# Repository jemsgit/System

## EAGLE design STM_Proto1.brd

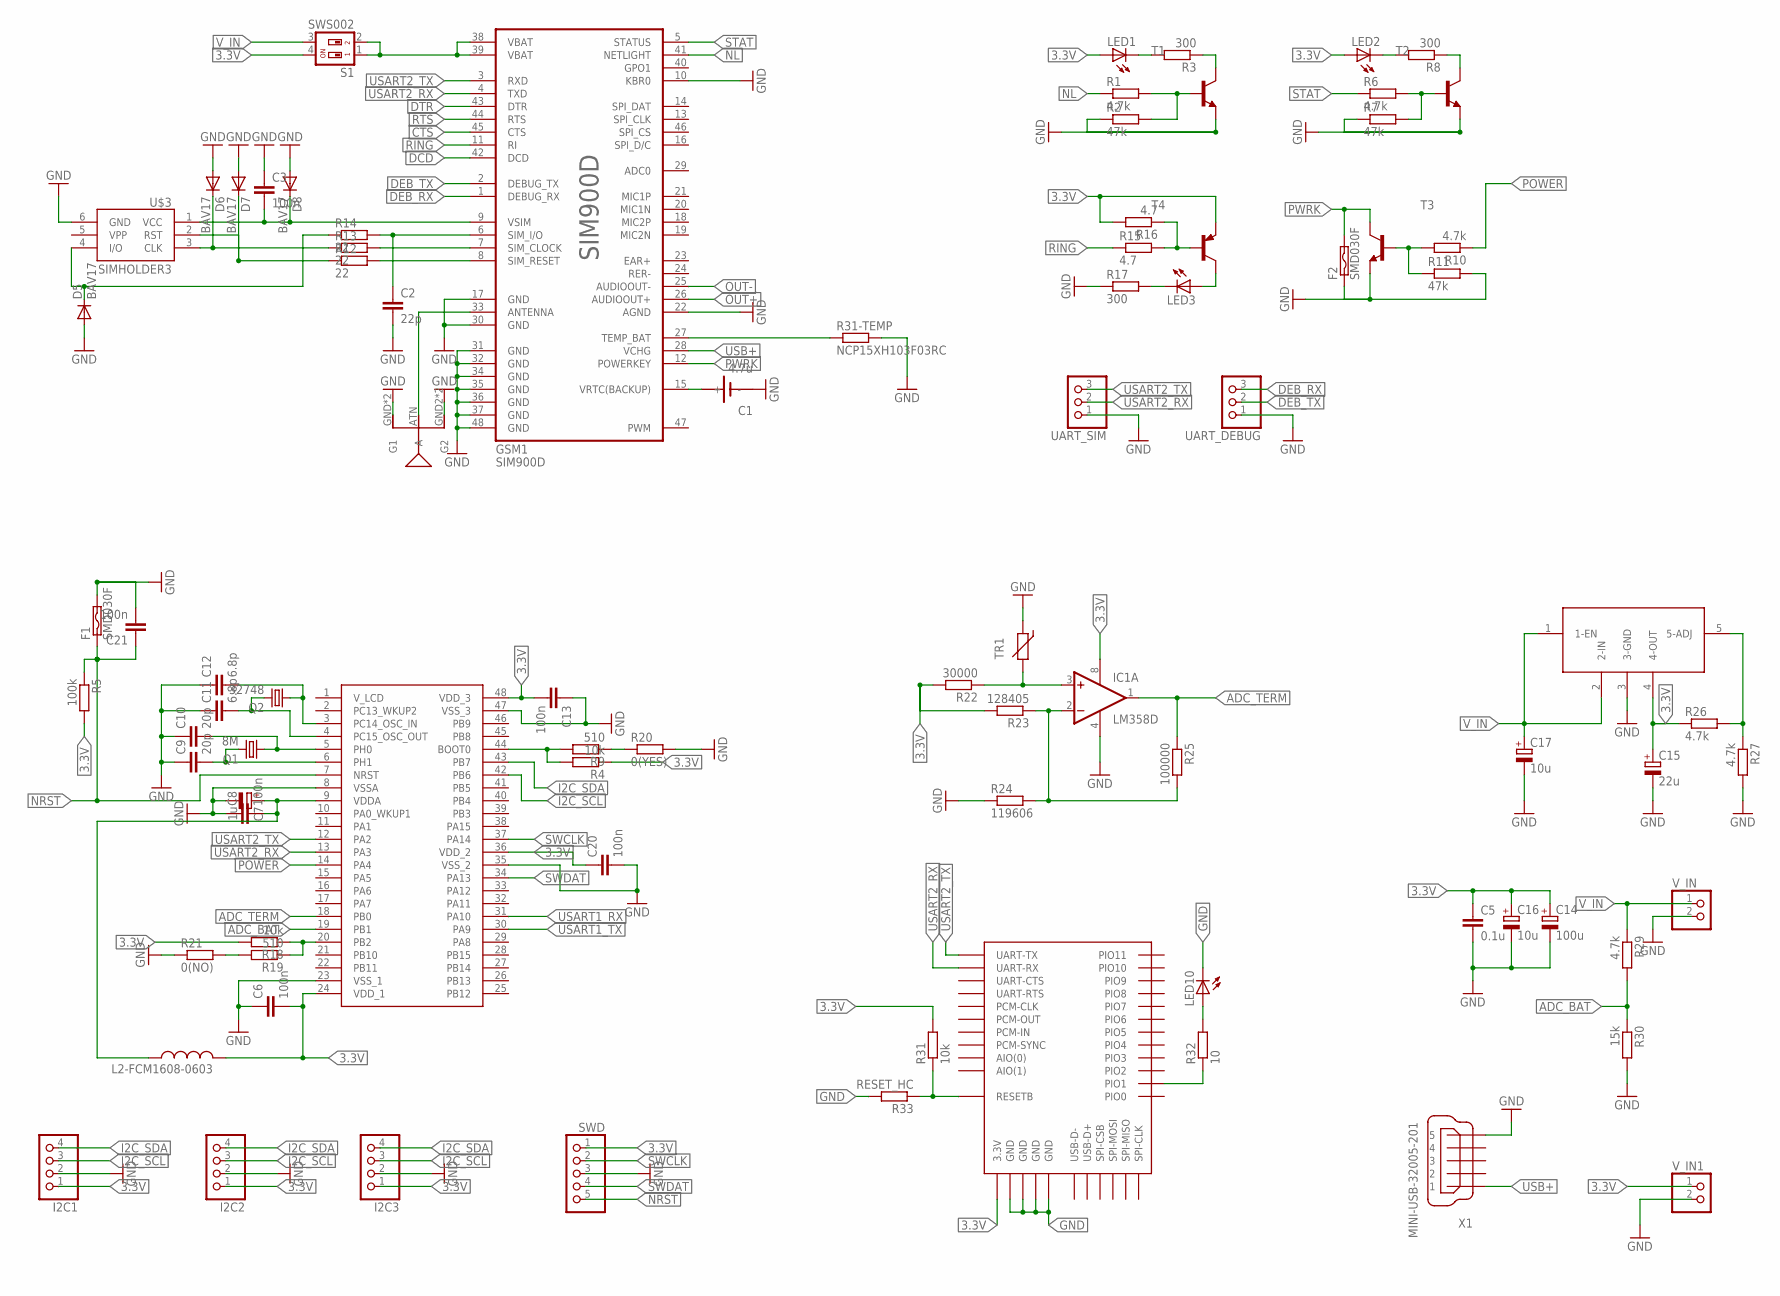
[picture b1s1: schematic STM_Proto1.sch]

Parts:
C1: 4.7u; SN2032
C2: 22p; C1206
C3, C6, C8, C13, C20, C21: 100n; C0805
C5: 0.1u; C0805
C7: 1u; 153CLV-0405
C9, C10: 20p; C0805
C11, C12: 6.8p; C0805
C14: 100u; 153CLV-0807
C15: 22u; 153CLV-0605
C16, C17: 10u; 153CLV-0505
D5, D6, D7, D8: BAV17; DO35-10
F1, F2: SMD030F; SMD050F
GSM1: SIM900D
I2C1, I2C2, I2C3: PINHD-1X4; 1X04
IC1: LM358D; SO08
L2-FCM1608-0603: L-USL3216C; L3216C
LED1, LED2, LED3: LEDSMT1206; 1206
LED10: LEDCHIPLED_1206; CHIPLED_1206
Q1: 8M; HC49/S
Q2: 32748; TC26H
R1, R6, R10, R26, R27, R29: 4.7k; R0805
R2, R7, R11: 47k; R0805
R3, R8, R17: 300; R0805
R4: 10k; R0805
R5: 100k; R0805
R9, R19: 510; R0805
R12, R13, R14: 22; R0805
R15, R16: 4.7; R0805
R18, R31: 10k; M0805
R20: 0(YES); R1206
R21: 0(NO); R1206
R22: 30000; R0805
R23: 128405; R0805
R24: 119606; R0805
R25: 100000; R0805
R30: 15k; R0805
R31-TEMP: NCP15XH103F03RC; M0805
R32: 10; M0805
R33: RESET_HC; M0805
S1: SWS002; SMS-002
STM32L152CBT6: STM32L152C6; LQFP48
SWD: PINHD-1X5; 1X05
T1, T2, T3: BC846B-NPN-SOT23-BEC; SOT23-BEC
T4: BC858CLT1-PNP-SOT23-BEC; SOT23-BEC
TR1: THERMISTOR_R-7,5; R-7,5
U$2: GSM_ANT; GSM
U$3: SIMHOLDER3
U$4: BTM400_6B
U$5: MIC29302WT; TO263-5
UART_DEBUG: PINHD-1X3; 1X03
UART_SIM: PINHD-1X3; 1X03
V_IN, V_IN1: PINHD-1X2; 1X02
X1: MINI-USB-32005-201; 32005-201

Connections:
3.3V: C5.1, C6.2, C13.2, C14.+, C15.+, C16.+, C20.1, I2C1.1, I2C2.1, I2C3.1, IC1.8 (V+), L2-FCM1608-0603.2, LED1.A, LED2.A, R4.1, R5.2, R16.2, R18.2, R22.2, R23.2, R26.1, R31.2, S1.4, STM32L152CBT6.24 (VDD_1), STM32L152CBT6.36 (VDD_2), STM32L152CBT6.48 (VDD_3), SWD.1, T4.E, U$4.3.3V, U$5.4 (4-OUT), V_IN1.1
ADC_BAT: R29.2, R30.1, STM32L152CBT6.19 (PB1)
ADC_TERM: IC1.1 (OUT), R25.1, STM32L152CBT6.18 (PB0)
CTS: GSM1.45 (CTS)
DCD: GSM1.42 (DCD)
DEB_RX: GSM1.1 (DEBUG_RX), UART_DEBUG.3
DEB_TX: GSM1.2 (DEBUG_TX), UART_DEBUG.2
DTR: GSM1.43 (DTR)
GND: C1.-, C2.2, C3.1, C5.2, C6.1, C7.-, C8.1, C9.1, C10.1, C11.1, C12.1, C13.1, C14.-, C15.-, C16.-, C17.-, C20.2, C21.2, D5.A, D6.A, D7.A, D8.A, F1.2, F2.1, GSM1.10 (KBR0), GSM1.17 (GND), GSM1.22 (AGND), GSM1.30 (GND), GSM1.31 (GND), GSM1.32 (GND), GSM1.34 (GND), GSM1.35 (GND), GSM1.36 (GND), GSM1.37 (GND), GSM1.48 (GND), I2C1.2, I2C2.2, I2C3.2, IC1.4 (V-), LED10.C, R2.1, R7.1, R11.2, R17.1, R20.2, R21.1, R24.1, R27.2, R30.2, R31-TEMP.2, R33.2, STM32L152CBT6.8 (VSSA), STM32L152CBT6.23 (VSS_1), STM32L152CBT6.35 (VSS_2), STM32L152CBT6.47 (VSS_3), SWD.3, T1.E, T2.E, T3.E, TR1.1, U$2.GND (G1), U$2.GND1 (G1), U$2.GND2 (G2), U$2.GND3 (G2), U$3.6 (GND), U$4.GND@1 (GND), U$4.GND@2 (GND), U$4.GND@3 (GND), U$4.GND@4 (GND), U$5.3 (3-GND), UART_DEBUG.1, UART_SIM.1, V_IN.2, V_IN1.2, X1.5
I2C_SCL: I2C1.3, I2C2.3, I2C3.3, STM32L152CBT6.42 (PB6)
I2C_SDA: I2C1.4, I2C2.4, I2C3.4, STM32L152CBT6.43 (PB7)
unnamed: R10.2, R11.1, T3.B
unnamed: C10.2, Q1.1, STM32L152CBT6.5 (PH0)
unnamed: LED1.C, R3.2
unnamed: R1.2, R2.2, T1.B
unnamed: R3.1, T1.C
unnamed: R31.1, R33.1, U$4.RESETB
unnamed: R6.2, R7.2, T2.B
unnamed: R8.1, T2.C
unnamed: C3.2, D8.C, GSM1.9 (VSIM), U$3.1 (VCC)
unnamed: LED2.C, R8.2
unnamed: IC1.2 (-IN), R23.1, R24.2, R25.2
unnamed: IC1.3 (+IN), R22.1, TR1.2
unnamed: D7.C, R12.1, U$3.2 (RST)
unnamed: GSM1.8 (SIM_RESET), R12.2
unnamed: D6.C, R13.1, U$3.3 (CLK)
unnamed: GSM1.7 (SIM_CLOCK), R13.2
unnamed: D5.C, R14.1, U$3.4 (I/O)
unnamed: C2.1, GSM1.6 (SIM_I/O), R14.2
unnamed: GSM1.27 (TEMP_BAT), R31-TEMP.1
unnamed: R32.1, U$4.PIO(1) (PIO1)
unnamed: R15.2, R16.1, T4.B
unnamed: GSM1.33 (ANTENNA), U$2.ATN (A)
unnamed: LED3.A, T4.C
unnamed: LED3.C, R17.2
unnamed: C9.2, Q1.2, STM32L152CBT6.6 (PH1)
unnamed: C11.2, Q2.2, STM32L152CBT6.4 (PC15_OSC_OUT)
unnamed: C12.2, Q2.1, STM32L152CBT6.3 (PC14_OSC_IN)
unnamed: C7.+, C8.2, L2-FCM1608-0603.1, STM32L152CBT6.9 (VDDA)
unnamed: R4.2, R9.2, STM32L152CBT6.44 (BOOT0)
unnamed: LED10.A, R32.2
unnamed: R9.1, R20.1
unnamed: R18.1, R19.1, STM32L152CBT6.20 (PB2)
unnamed: R19.2, R21.2
unnamed: R26.2, R27.1, U$5.5 (5-ADJ)
NL: GSM1.41 (NETLIGHT), R1.1
NRST: C21.1, F1.1, R5.1, STM32L152CBT6.7 (NRST), SWD.5
OUT+: GSM1.26 (AUDIOOUT+)
OUT-: GSM1.25 (AUDIOOUT-)
POWER: R10.1, STM32L152CBT6.14 (PA4)
PWRK: F2.2, GSM1.12 (POWERKEY), T3.C
RING: GSM1.11 (RI), R15.1
RTS: GSM1.44 (RTS)
STAT: GSM1.5 (STATUS), R6.1
SWCLK: STM32L152CBT6.37 (PA14), SWD.2
SWDAT: STM32L152CBT6.34 (PA13), SWD.4
USART1_RX: STM32L152CBT6.31 (PA10)
USART1_TX: STM32L152CBT6.30 (PA9)
USART2_RX: GSM1.4 (TXD), STM32L152CBT6.13 (PA3), U$4.UART-RX, UART_SIM.2
USART2_TX: GSM1.3 (RXD), STM32L152CBT6.12 (PA2), U$4.UART-TX, UART_SIM.3
USB+: GSM1.28 (VCHG), X1.1
VBAT@2: GSM1.38 (VBAT), GSM1.39 (VBAT), S1.1, S1.2
VRTC(BACKUP): C1.+, GSM1.15 (VRTC(BACKUP))
V_IN: C17.+, R29.1, S1.3, U$5.1 (1-EN), U$5.2 (2-IN), V_IN.1

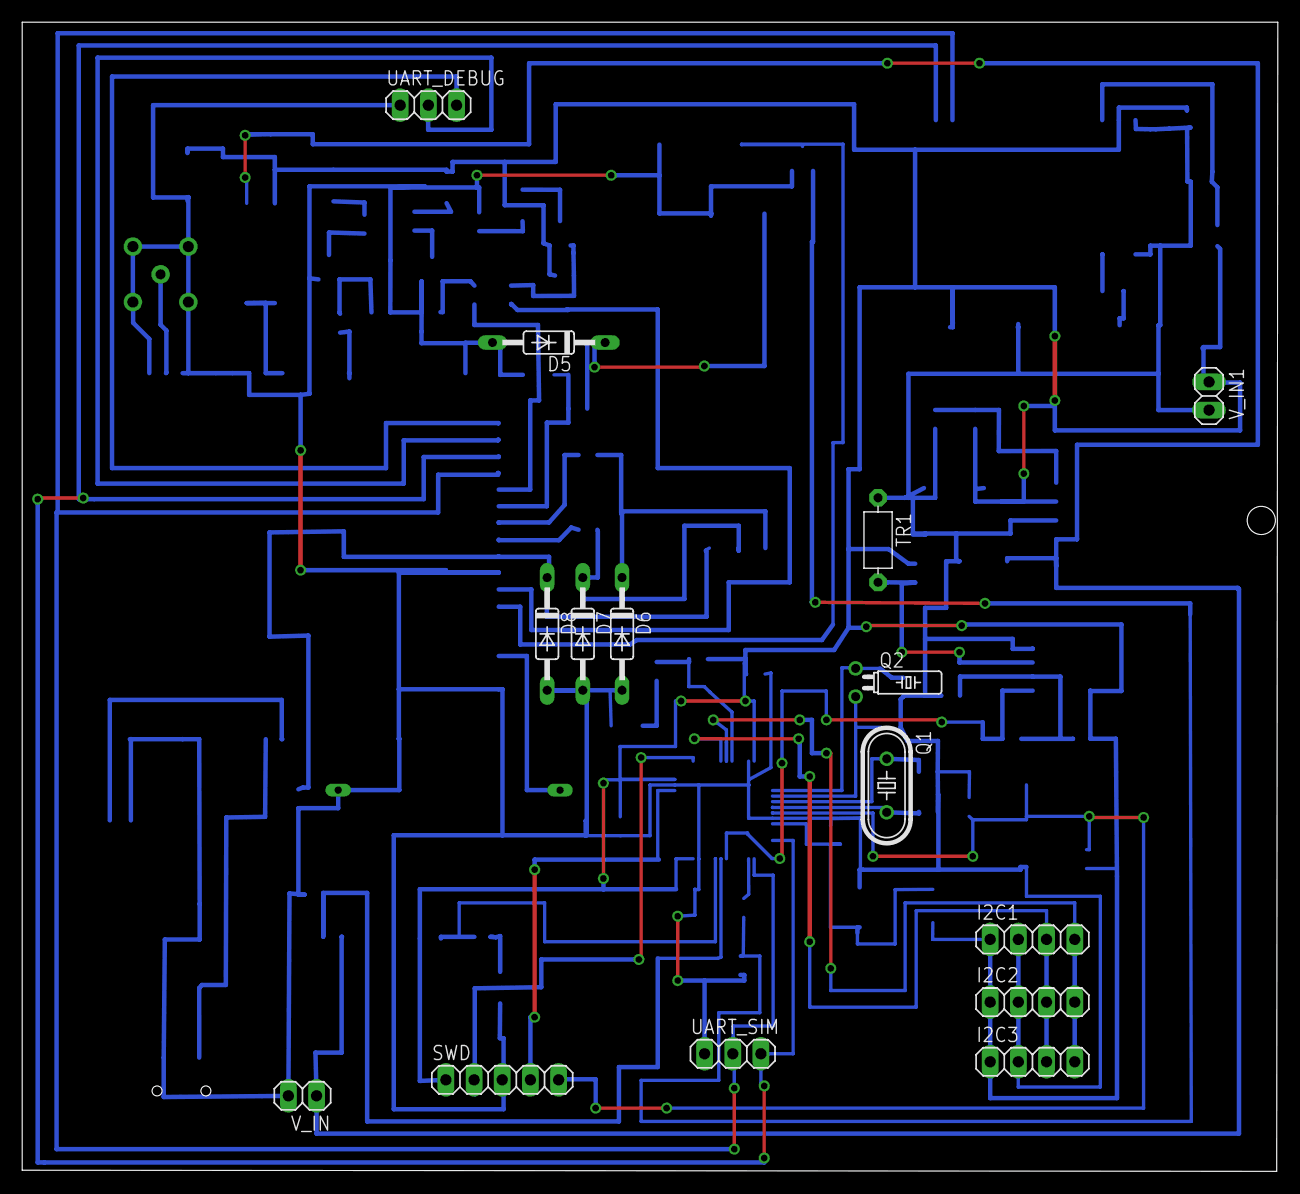
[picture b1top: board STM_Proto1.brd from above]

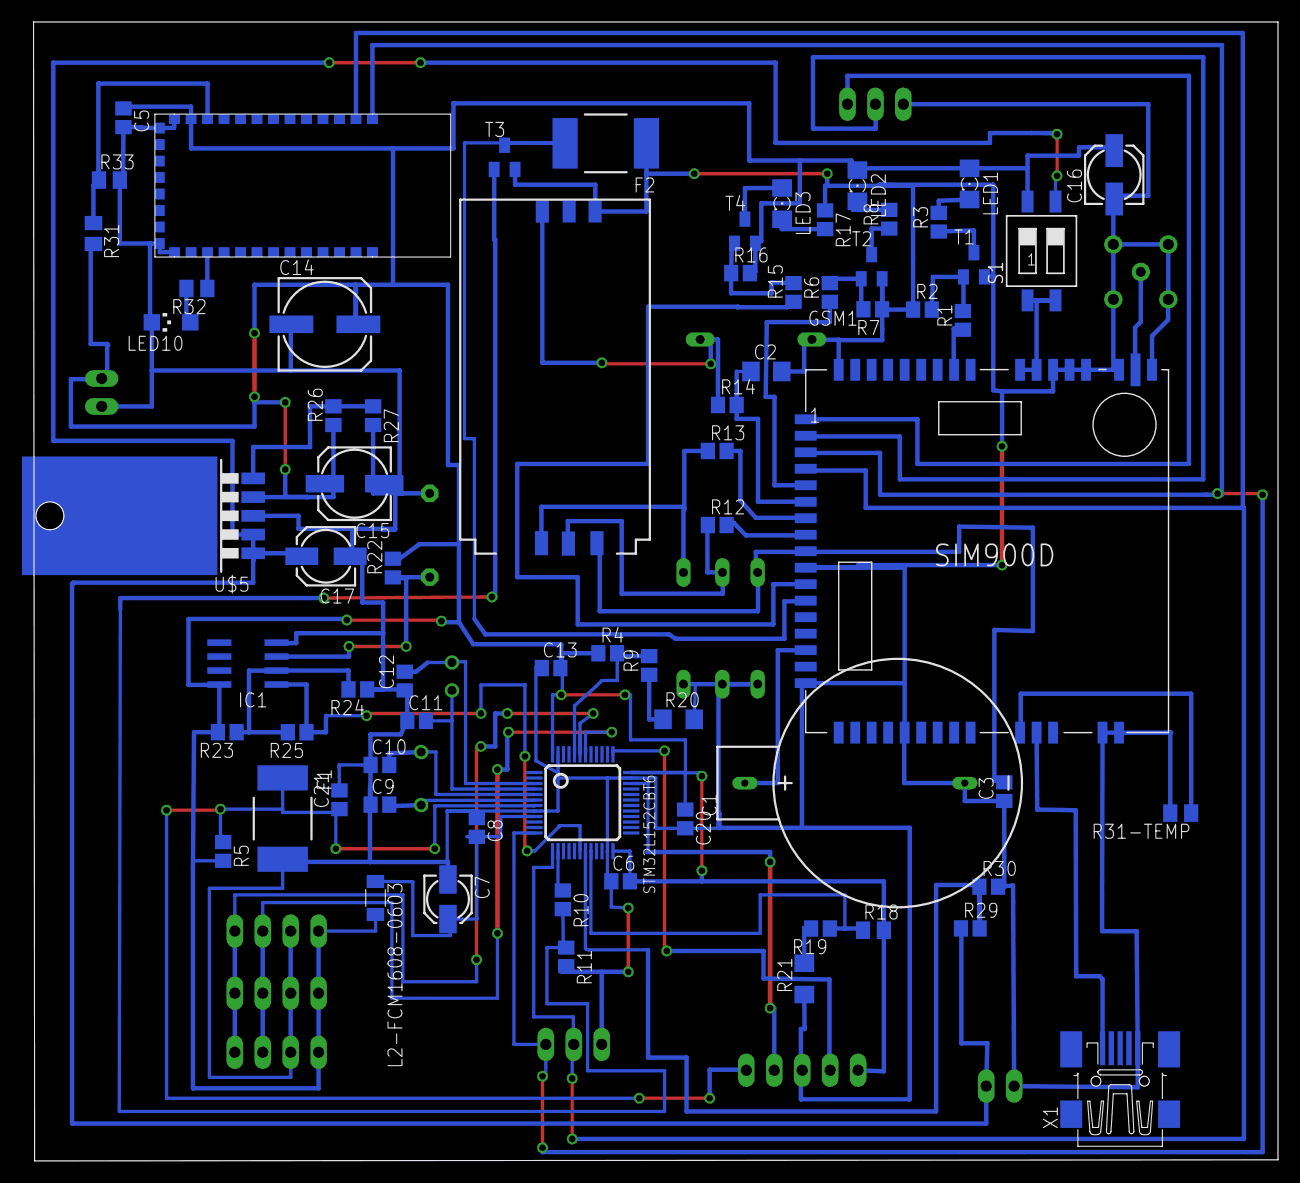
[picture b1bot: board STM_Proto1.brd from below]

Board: 2 copper layers, 113.2 x 103.6 mm, 86 parts (70 on the bottom side), 56 nets.

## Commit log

2014-08-18 First sch & brd
2014-08-18 Update 1
2014-08-18 Update 2
2014-08-20 Libraries for Simholder and HM-10
2014-08-20 Libraries for Simholder and HM-10-2
2014-08-21 Add Charger
2014-12-21 Last version with SIM900D

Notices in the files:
parts and their libraries:
SparkFun-Connectors: Licensing: CC v3.0 Share-Alike You are welcome to use this library for commercial purposes.
